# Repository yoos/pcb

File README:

Nothing too far out of the ordinary here, since I'm a programmer, not an electronics whiz. But I know enough electronics with which to build robots, and these are some of my attempts at PCB design.

As of 3/25/12, I've decided that all of my circuits will be designed in EAGLE, since SparkFun has a gigantic EAGLE library and the interface is not significantly worse than KiCAD.

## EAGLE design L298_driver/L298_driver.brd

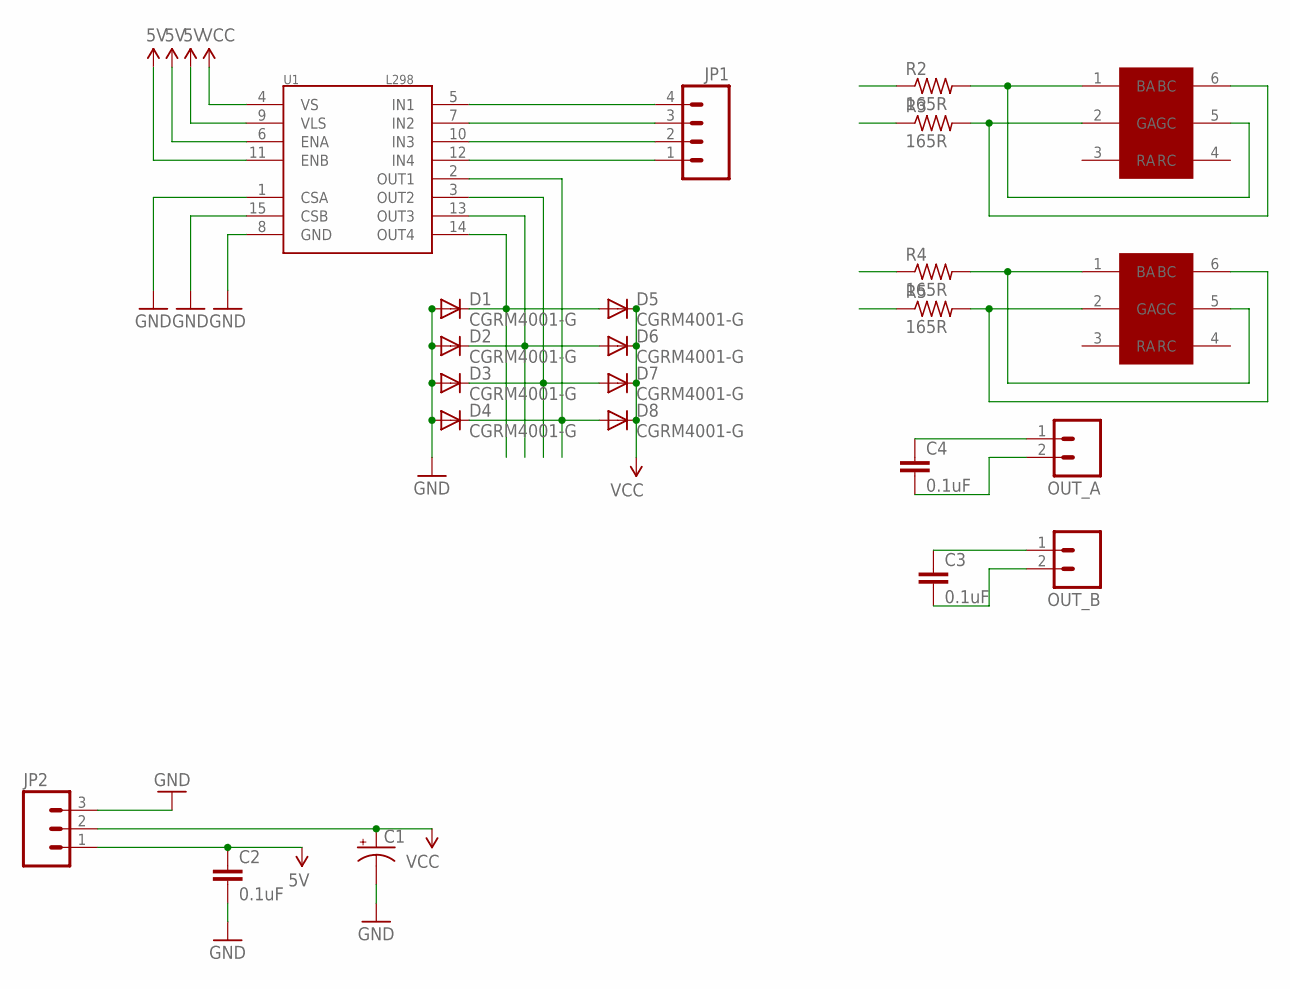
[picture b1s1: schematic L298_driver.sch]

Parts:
C1: CPOL-USTT5D11L; TT5D11L
C2, C3, C4: 0.1uF; 0402-CAP
D1, D2, D3, D4, D5, D6, D7, D8: CGRM4001-G; SOD-123_MINI-SMA
JP1: M04POLAR; MOLEX-1X4
JP2: M03-SCREW-5MM; SCREWTERMINAL-5MM-3
LED_A: LRTB_R98G; 6-SMD
LED_B: LRTB_R98G; 6-SMD
OUT_A: M025MM; SCREWTERMINAL-5MM-2
OUT_B: M025MM; SCREWTERMINAL-5MM-2
R2, R3, R4, R5: 165R; R0402
U1: L298; MULTIWATT15

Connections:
5V: C2.1, JP2.1, U1.6 (ENA), U1.9 (VLS), U1.11 (ENB)
GND: C1.-, C2.2, D1.A, D2.A, D3.A, D4.A, JP2.3, U1.1 (CSA), U1.8 (GND), U1.15 (CSB)
IN1: JP1.4, R2.1, U1.5 (IN1)
IN2: JP1.3, R3.1, U1.7 (IN2)
IN3: JP1.2, R4.1, U1.10 (IN3)
IN4: JP1.1, R5.1, U1.12 (IN4)
unnamed: LED_A.1 (BA), LED_A.5 (GC), R2.2
unnamed: LED_A.2 (GA), LED_A.6 (BC), R3.2
unnamed: LED_B.1 (BA), LED_B.5 (GC), R4.2
unnamed: LED_B.2 (GA), LED_B.6 (BC), R5.2
OUT1: C4.1, D4.C, D8.A, OUT_A.1, U1.2 (OUT1)
OUT2: C4.2, D3.C, D7.A, OUT_A.2, U1.3 (OUT2)
OUT3: C3.1, D2.C, D6.A, OUT_B.1, U1.13 (OUT3)
OUT4: C3.2, D1.C, D5.A, OUT_B.2, U1.14 (OUT4)
VCC: C1.+, D5.C, D6.C, D7.C, D8.C, JP2.2, U1.4 (VS)

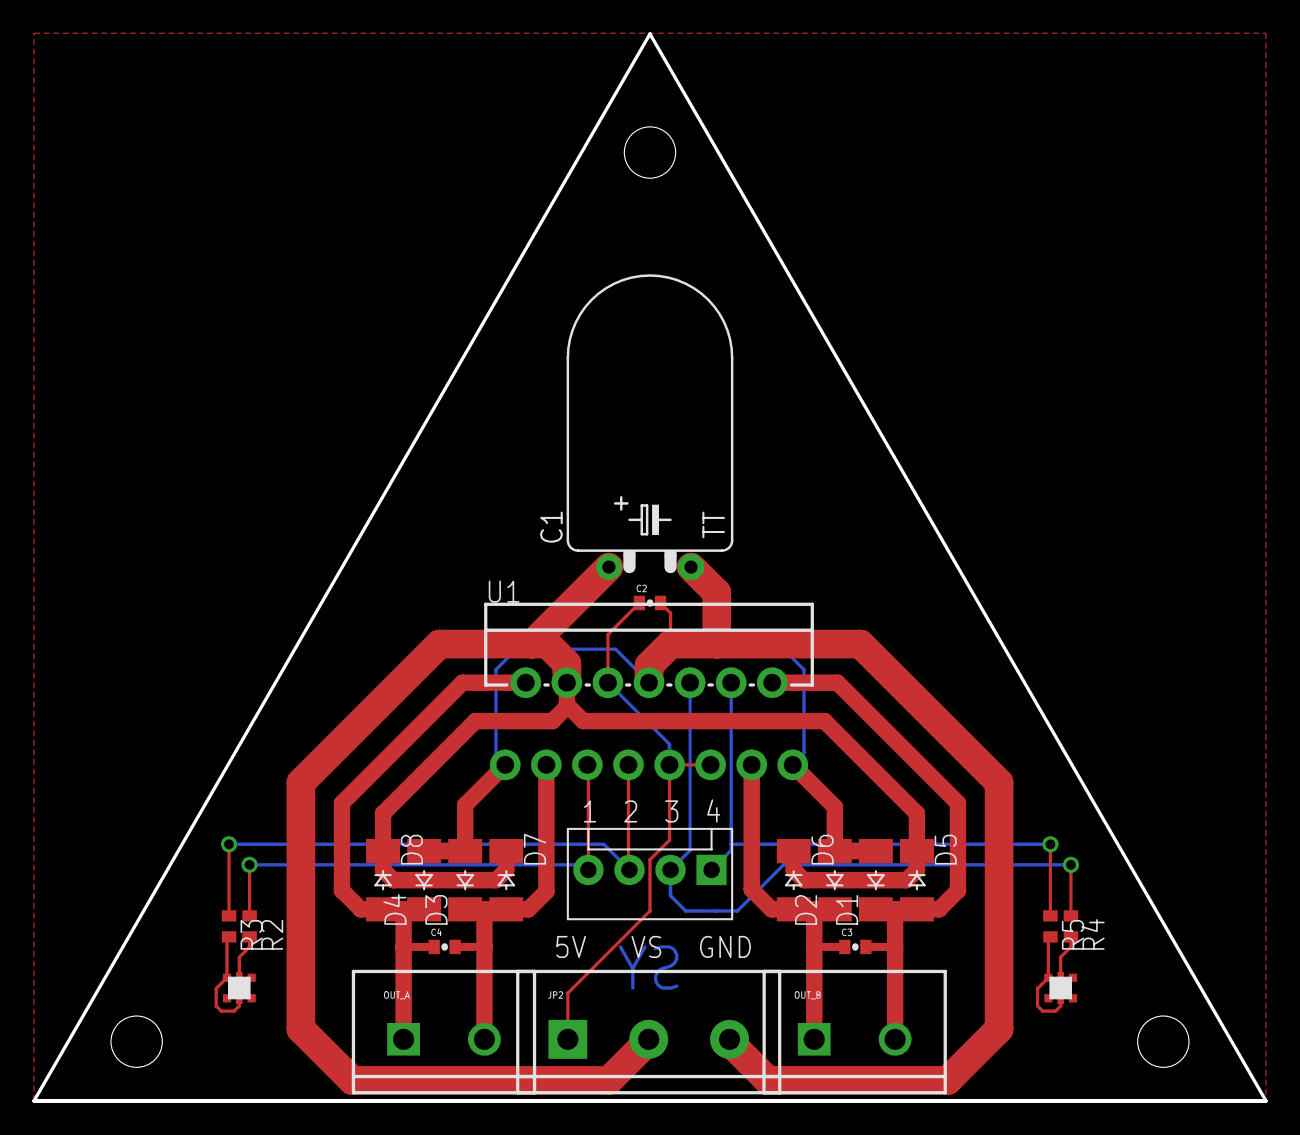
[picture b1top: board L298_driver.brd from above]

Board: 2 copper layers, 76.2 x 66.0 mm, 23 parts (0 on the bottom side), 15 nets.

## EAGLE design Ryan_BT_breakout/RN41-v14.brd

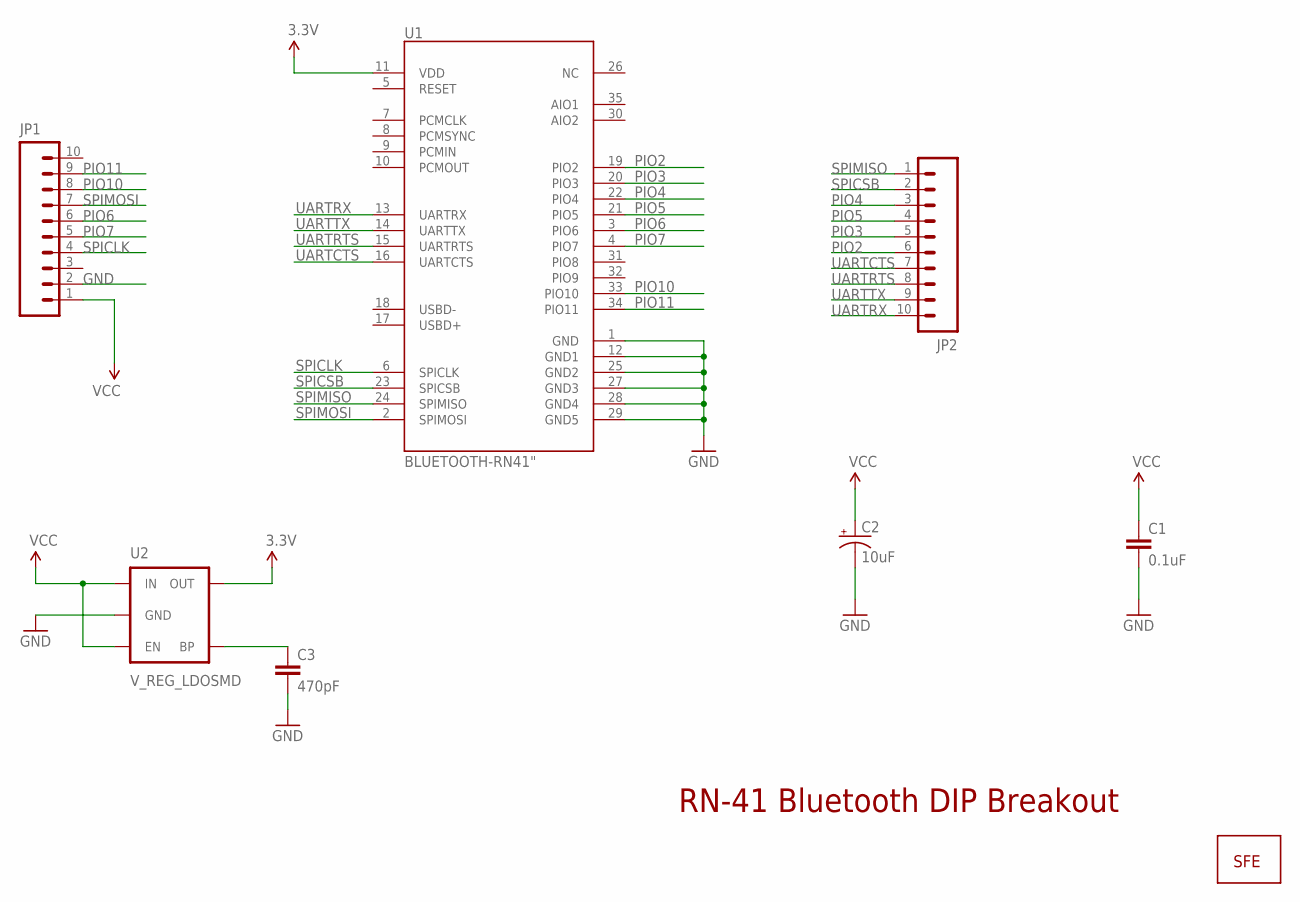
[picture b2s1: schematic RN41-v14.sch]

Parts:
C1: 0.1uF; 0603-CAP
C2: 10uF; EIA3216
C3: 470pF; 0603-CAP
JP1, JP2: M10"; 1X10
U1: BLUETOOTH-RN41"; RN41
U2: V_REG_LDOSMD; SOT23-5
U$1: LOGO-SFENEW; SFE-NEW-WEBLOGO

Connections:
3.3V: U1.11 (VDD), U2.5 (OUT)
GND: C1.2, C2.C (-), C3.2, JP1.2, U1.1 (GND), U1.12 (GND1), U1.25 (GND2), U1.27 (GND3), U1.28 (GND4), U1.29 (GND5), U2.2 (GND)
unnamed: C3.1, U2.4 (BP)
PIO2: JP2.6, U1.19 (PIO2)
PIO3: JP2.5, U1.20 (PIO3)
PIO4: JP2.3, U1.22 (PIO4)
PIO5: JP2.4, U1.21 (PIO5)
PIO6: JP1.6, U1.3 (PIO6)
PIO7: JP1.5, U1.4 (PIO7)
PIO10: JP1.8, U1.33 (PIO10)
PIO11: JP1.9, U1.34 (PIO11)
SPICLK: JP1.4, U1.6 (SPICLK)
SPICSB: JP2.2, U1.23 (SPICSB)
SPIMISO: JP2.1, U1.24 (SPIMISO)
SPIMOSI: JP1.7, U1.2 (SPIMOSI)
UARTCTS: JP2.7, U1.16 (UARTCTS)
UARTRTS: JP2.8, U1.15 (UARTRTS)
UARTRX: JP2.10, U1.13 (UARTRX)
UARTTX: JP2.9, U1.14 (UARTTX)
VCC: C1.1, C2.A (+), JP1.1, U2.1 (IN), U2.3 (EN)

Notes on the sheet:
RN-41 Bluetooth DIP Breakout

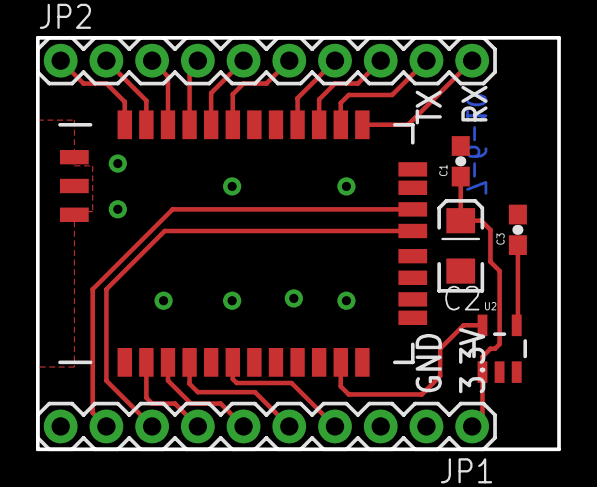
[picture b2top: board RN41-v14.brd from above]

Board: 2 copper layers, 29.0 x 22.9 mm, 8 parts (1 on the bottom side), 19 nets.

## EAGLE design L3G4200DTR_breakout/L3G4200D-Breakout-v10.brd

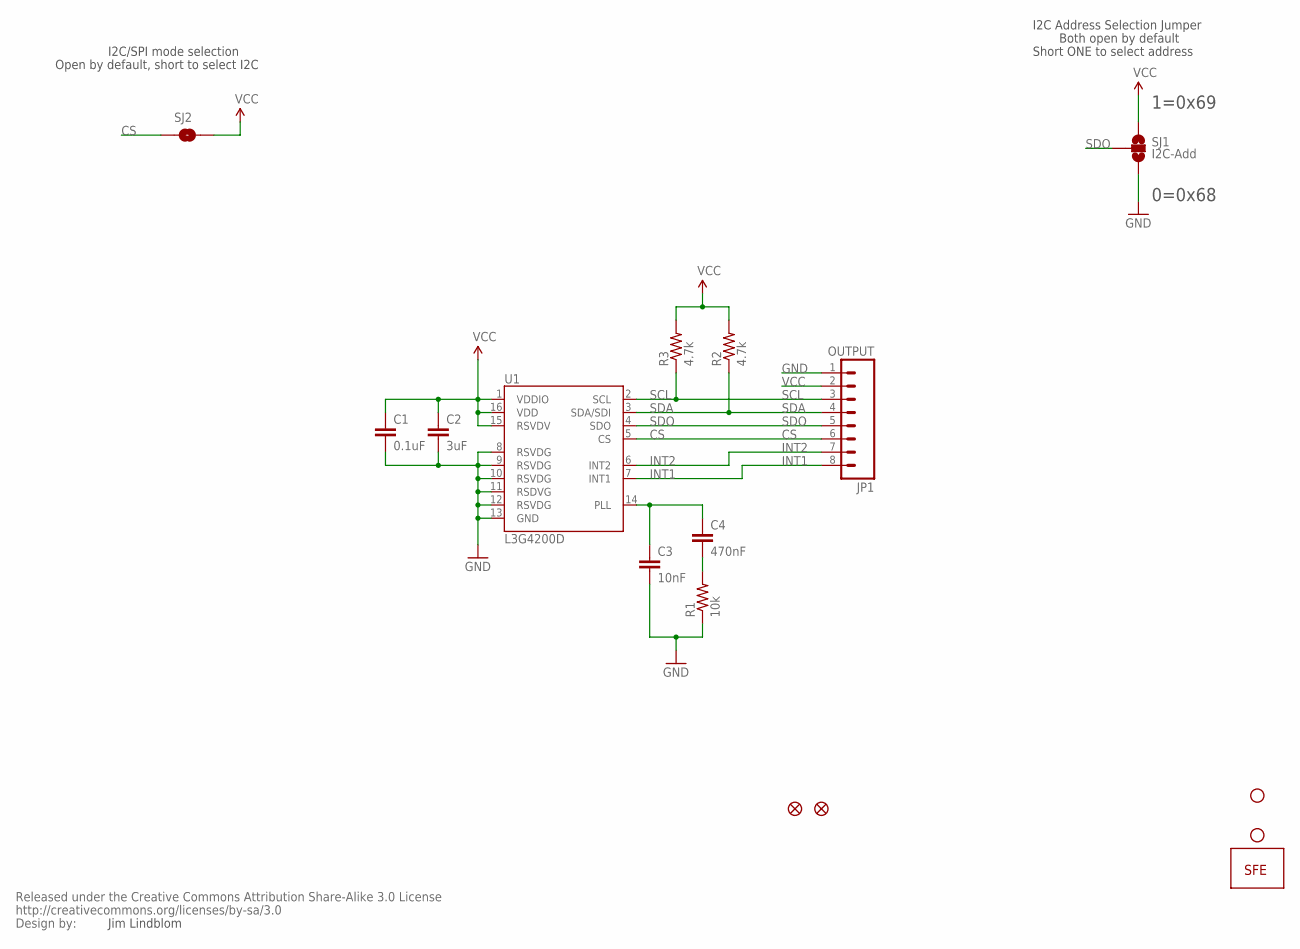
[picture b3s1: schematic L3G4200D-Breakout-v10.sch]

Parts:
C1: 0.1uF; 0603-CAP
C2: 3uF; 0603-CAP
C3: 10nF; 0603-CAP
C4: 470nF; 0603-CAP
JP1: OUTPUT; 1X08
JP2, JP3: STAND-OFF
JP4: LOGO-SFESK; SFE-LOGO-FLAME
JP5, JP6: FIDUCIAL1X2; FIDUCIAL-1X2
R1: 10k; 0603-RES
R2, R3: 4.7k; 0603-RES
SJ1: I2C-Add; SJ_3
SJ2: I2C-Mode; SJ_2S-NO
U1: L3G4200D; LGA16-4X4
U$1: CREATIVE_COMMONS

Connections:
CS: JP1.6, SJ2.1, U1.5 (CS)
GND: C1.2, C2.2, C3.2, JP1.1, R1.1, SJ1.3, U1.8 (RSVDG), U1.9 (RSVDG), U1.10 (RSVDG), U1.11 (RSDVG), U1.12 (RSVDG), U1.13 (GND)
INT1: JP1.8, U1.7 (INT1)
INT2: JP1.7, U1.6 (INT2)
PLL: C3.1, C4.1, U1.14 (PLL)
PLL-2: C4.2, R1.2
SCL: JP1.3, R3.1, U1.2 (SCL)
SDA: JP1.4, R2.1, U1.3 (SDA/SDI)
SDO: JP1.5, SJ1.2, U1.4 (SDO)
VCC: C1.1, C2.1, JP1.2, R2.2, R3.2, SJ1.1, SJ2.2, U1.1 (VDDIO), U1.15 (RSVDV), U1.16 (VDD)

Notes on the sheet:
I2C Address Selection Jumper
Jim Lindblom
Both open by default
1=0x69
0=0x68
Short ONE to select address
I2C/SPI mode selection
Open by default, short to select I2C

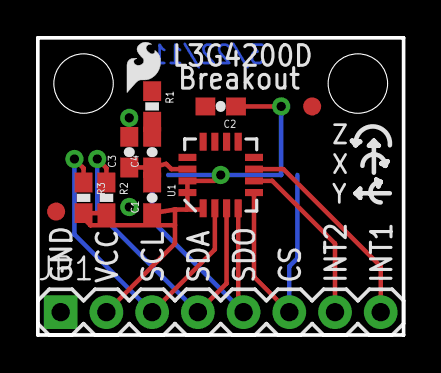
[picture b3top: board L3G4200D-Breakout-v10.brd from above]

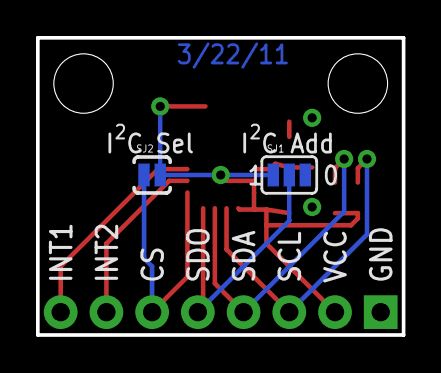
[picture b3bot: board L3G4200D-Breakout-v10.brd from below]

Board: 2 copper layers, 20.3 x 16.5 mm, 17 parts (2 on the bottom side), 10 nets.

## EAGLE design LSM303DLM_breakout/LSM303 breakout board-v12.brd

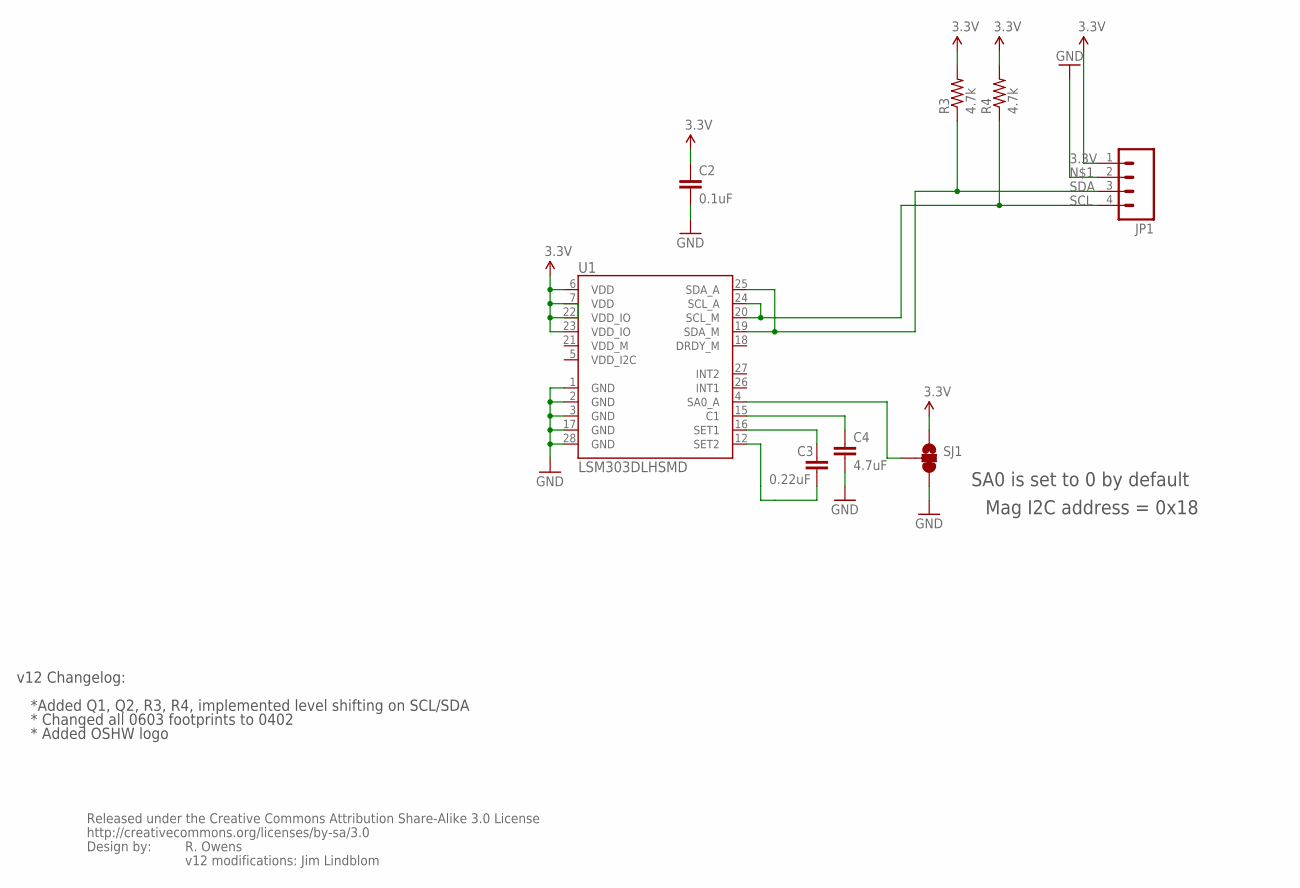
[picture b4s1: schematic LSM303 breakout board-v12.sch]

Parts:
C2: 0.1uF; 0603-CAP
C3: 0.22uF; 0603-CAP
C4: 4.7uF; 1206
JP1: M04PTH; 1X04
R3, R4: 4.7k; 0805
SJ1: SOLDERJUMPER_2WAYPASTE2&3; SJ_3_PASTE2&3
U1: LSM303DLHSMD; LGA28-5X5
U$5: CREATIVE_COMMONS

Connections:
3.3V: C2.1, JP1.1, R3.2, R4.2, SJ1.1, U1.6 (VDD), U1.7 (VDD), U1.23 (VDD_IO)
unnamed: C2.2, C4.2, JP1.2, SJ1.3, U1.1 (GND), U1.2 (GND), U1.3 (GND), U1.17 (GND), U1.28 (GND)
unnamed: C3.1, U1.16 (SET1)
unnamed: C3.2, U1.12 (SET2)
unnamed: C4.1, U1.15 (C1)
SA0_A: SJ1.2, U1.4 (SA0_A)
SCL: JP1.4, R4.1, U1.20 (SCL_M), U1.24 (SCL_A)
SDA: JP1.3, R3.1, U1.19 (SDA_M), U1.25 (SDA_A)

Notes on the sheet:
R. Owens
v12 modifications: Jim Lindblom
v12 Changelog:
*Added Q1, Q2, R3, R4, implemented level shifting on SCL/SDA
* Changed all 0603 footprints to 0402
SA0 is set to 0 by default
Mag I2C address = 0x18
* Added OSHW logo

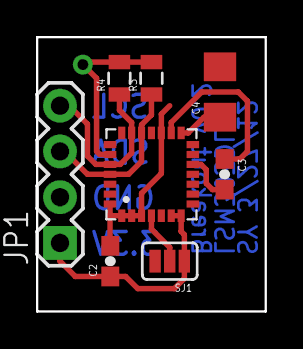
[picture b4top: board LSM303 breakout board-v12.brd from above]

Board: 2 copper layers, 12.7 x 15.2 mm, 9 parts (0 on the bottom side), 8 nets.

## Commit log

2012-03-25 Add breakout board for LSM303DLM 3-axis accelerometer and 3-axis magnetometer.
2012-03-25 Add .gitignore.
2012-03-25 Add readme.
2012-03-25 Minor edit.
2012-03-25 Finished?
2012-03-26 Make traces thicker.
2012-03-27 Version 0.1.
2012-03-28 Version 0.2. Make board a lot simpler.
2012-03-31 Minor modifications.
2012-04-15 Add L298H motor driver.
2012-04-15 Rename to indicate KiCAD usage.
2012-11-03 Add SparkFun files for L3G4200DTR breakout board.
2012-11-03 Changes.
2012-11-05 Add Ryan's BT board.
2012-11-05 Finish Ryan's board.
2013-03-06 Add L298 driver board.
2013-03-07 Rearrange components to fit inside triangular board.
    Still need to find a place for LEDs and their resistors.
2013-03-07 Finish layout.
2013-03-07 Pour ground planes.
2013-03-07 Change resistor value for 3.3V operation.
2013-03-07 Finish up.
2013-03-07 Labels should be on tPlace layer, not Dimension.

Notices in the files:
parts and their libraries:
SparkFun-PowerIC: Licensing: CC v3.0 Share-Alike You are welcome to use this library for commercial purposes.
SparkFun: Released under the Creative Commons Attribution Share-Alike 3.0 License
SparkFun: http://creativecommons.org/licenses/by-sa/3.0
